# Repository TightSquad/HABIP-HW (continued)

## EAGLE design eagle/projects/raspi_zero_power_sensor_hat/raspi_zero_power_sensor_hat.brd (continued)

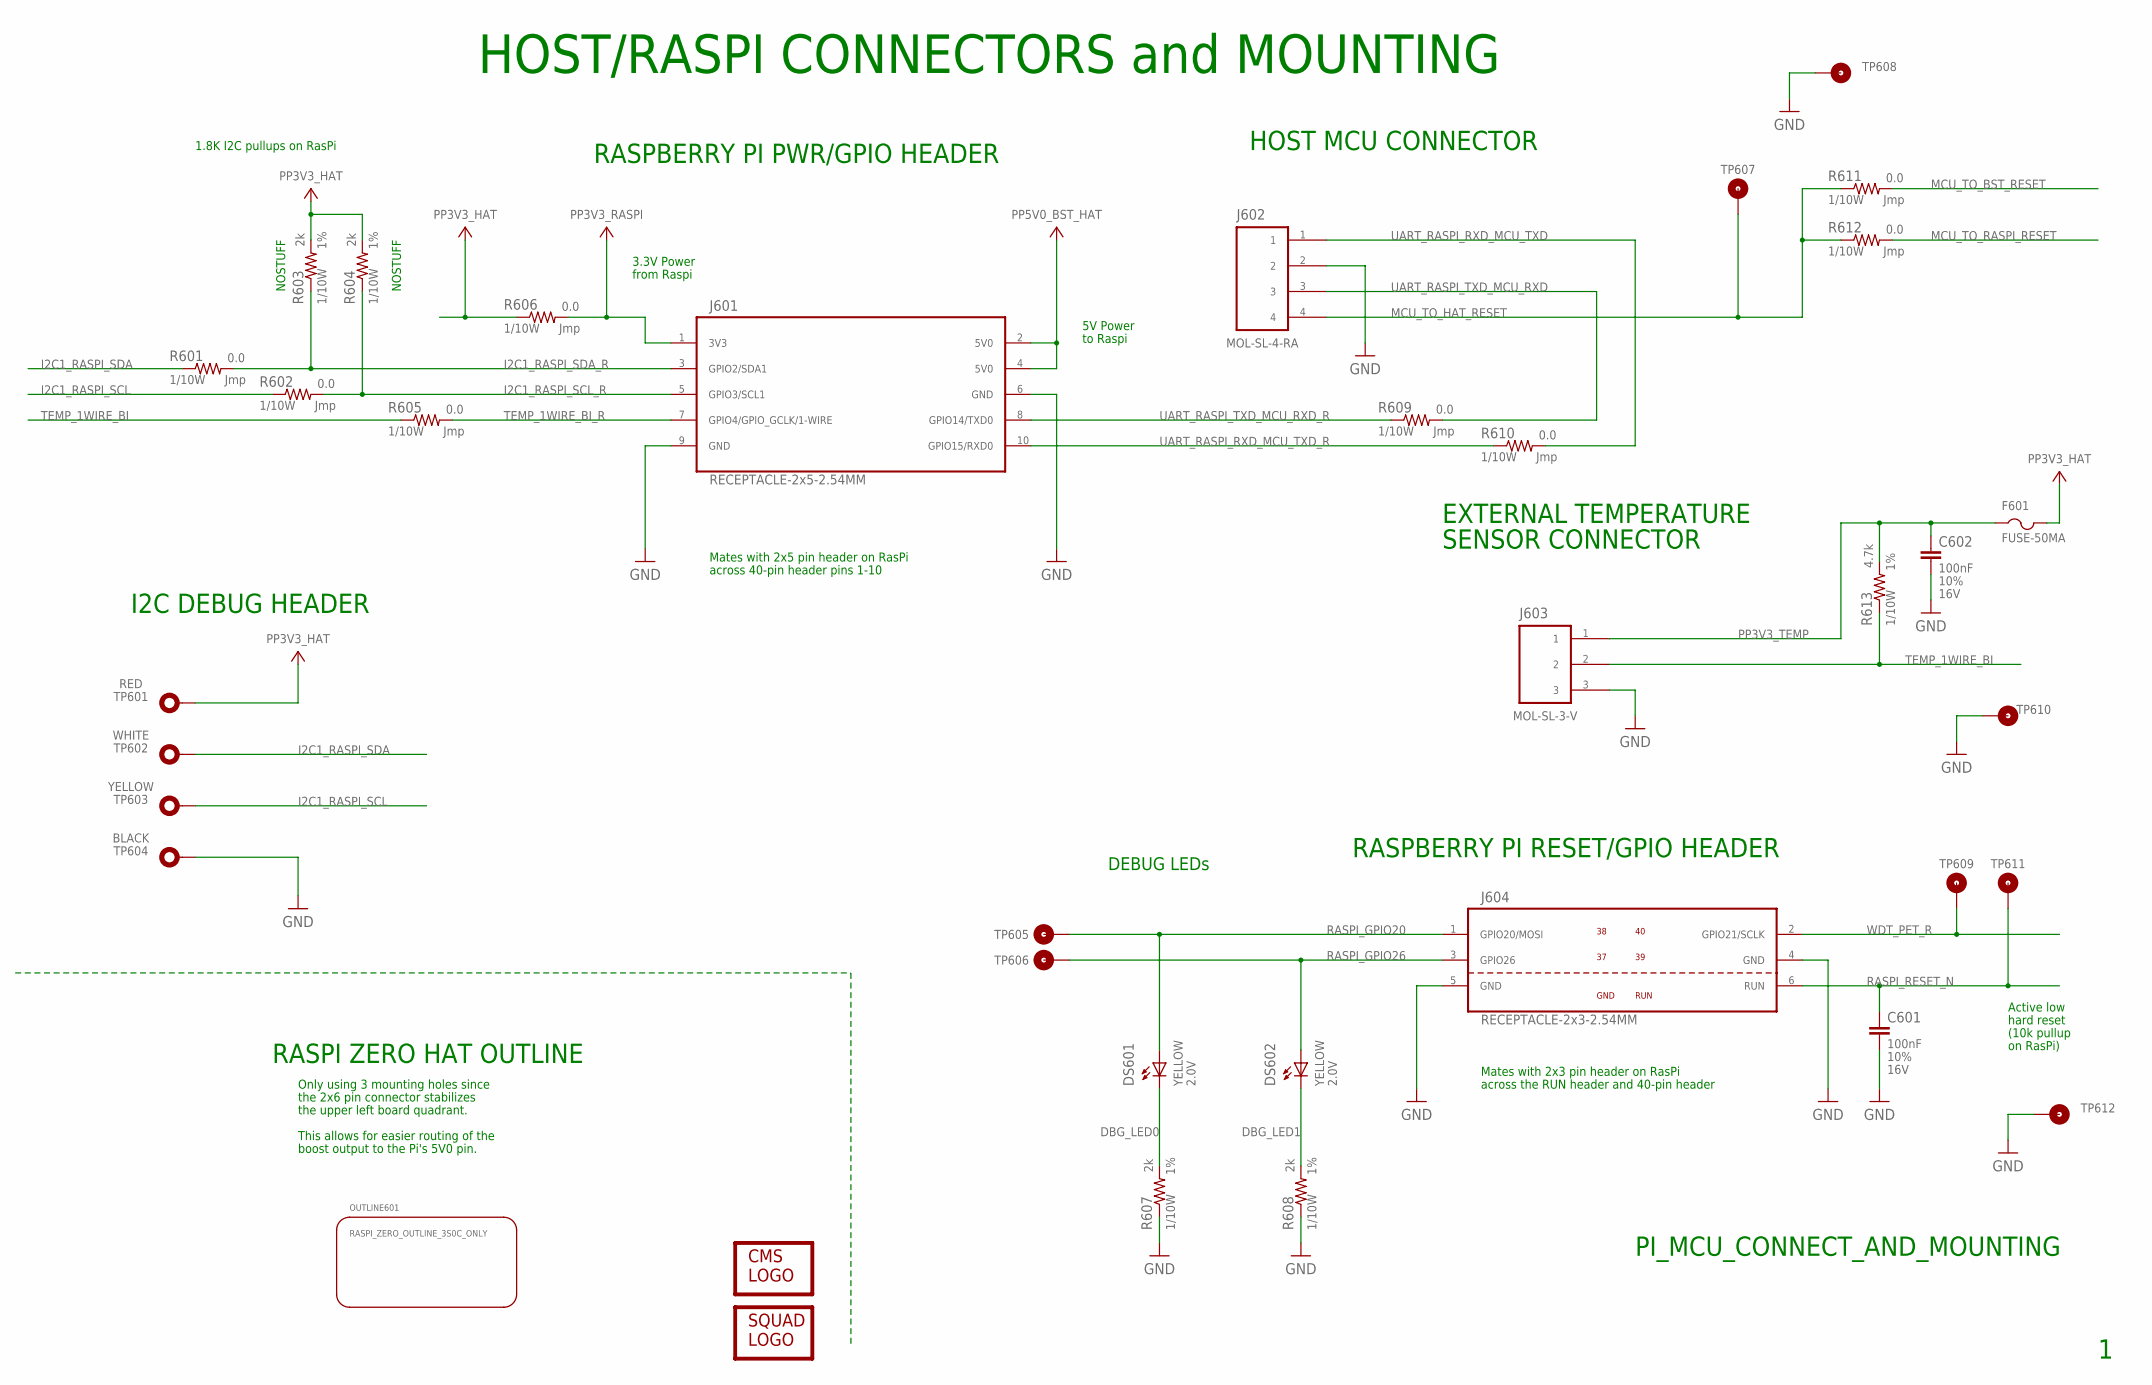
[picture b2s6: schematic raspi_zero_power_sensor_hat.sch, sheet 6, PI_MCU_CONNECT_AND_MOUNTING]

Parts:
C601, C602: 100nF; C0603
DS601, DS602: YELLOW; LED0603
F601: FUSE-50MA; R0603
J601: RECEPTACLE-2x5-2.54MM; RECEPTACLE-2X5-254MM
J602: MOL-SL-4-RA; MOLSL-4-RA_HALF
J603: MOL-SL-3-V; MOLSL-3-V
J604: RECEPTACLE-2x3-2.54MM; RECEPTACLE-2X3-254MM
LOGO601: CMS_LOGO
LOGO602: SQUAD_LOGO
OUTLINE601: RASPI_ZERO_OUTLINE_3S0C_ONLY; RASPI_ZERO_3STANDOFFS_ONLY
R601, R602, R605, R606, R609, R610, R611, R612: 0.0; R0603
R603, R604, R607, R608: 2k; R0603
R613: 4.7k; R0603
TP601: TEST_POINT_TH_D102_R; TP_TH102
TP602: TEST_POINT_TH_D102_W; TP_TH102
TP603: TEST_POINT_TH_D102_Y; TP_TH102
TP604: TEST_POINT_TH_D102_B; TP_TH102
TP605, TP606, TP607, TP608, TP609, TP610, TP611, TP612: TEST_POINT_SMT_15R_SMD; TP15R

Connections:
DBG_LED0: DS601.1 (C), R607.2
DBG_LED1: DS602.1 (C), R608.2
GND: C601.2, C602.2, J601.6 (GND), J601.9 (GND), J602.2, J603.3, J604.4 (GND), J604.5 (GND), R607.1, R608.1, TP604.1, TP608.TP, TP610.TP, TP612.TP; also elsewhere on the board
I2C1_RASPI_SCL: R602.1, TP603.1; also elsewhere on the board
I2C1_RASPI_SCL_R: J601.5 (GPIO3/SCL1), R602.2, R604.1
I2C1_RASPI_SDA: R601.1, TP602.1; also elsewhere on the board
I2C1_RASPI_SDA_R: J601.3 (GPIO2/SDA1), R601.2, R603.1
MCU_TO_BST_RESET: R611.2; also elsewhere on the board
MCU_TO_HAT_RESET: J602.4, R611.1, R612.1, TP607.TP
MCU_TO_RASPI_RESET: R612.2; also elsewhere on the board
PP3V3_HAT: F601.2, R603.2, R604.2, R606.1, TP601.1; also elsewhere on the board
PP3V3_RASPI: J601.1 (3V3), R606.2
PP3V3_TEMP: C602.1, F601.1, J603.1, R613.2
PP5V0_BST_HAT: J601.2 (5V0), J601.4 (5V0); also elsewhere on the board
RASPI_GPIO20: DS601.2 (A), J604.1 (GPIO20/MOSI), TP605.TP
RASPI_GPIO26: DS602.2 (A), J604.3 (GPIO26), TP606.TP
RASPI_RESET_N: C601.1, J604.6 (RUN), TP611.TP; also elsewhere on the board
TEMP_1WIRE_BI: J603.2, R605.1, R613.1
TEMP_1WIRE_BI_R: J601.7 (GPIO4/GPIO_GCLK/1-WIRE), R605.2
UART_RASPI_RXD_MCU_TXD: J602.1, R610.2
UART_RASPI_RXD_MCU_TXD_R: J601.10 (GPIO15/RXD0), R610.1
UART_RASPI_TXD_MCU_RXD: J602.3, R609.2
UART_RASPI_TXD_MCU_RXD_R: J601.8 (GPIO14/TXD0), R609.1
WDT_PET_R: J604.2 (GPIO21/SCLK), TP609.TP; also elsewhere on the board

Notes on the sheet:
PI_MCU_CONNECT_AND_MOUNTING
HOST/RASPI CONNECTORS and MOUNTING
RASPBERRY PI PWR/GPIO HEADER
5V Power
3.3V Power
from Raspi
to Raspi
HOST MCU CONNECTOR
EXTERNAL TEMPERATURE
SENSOR CONNECTOR
RASPI ZERO HAT OUTLINE
Only using 3 mounting holes since
the 2x6 pin connector stabilizes
the upper left board quadrant.
This allows for easier routing of the
boost output to the Pi's 5V0 pin.
I2C DEBUG HEADER
RASPBERRY PI RESET/GPIO HEADER
Active low
hard reset
Mates with 2x3 pin header on RasPi
across the RUN header and 40-pin header
Mates with 2x5 pin header on RasPi
across 40-pin header pins 1-10
NOSTUFF
DEBUG LEDs
(10k pullup
on RasPi)
1.8K I2C pullups on RasPi

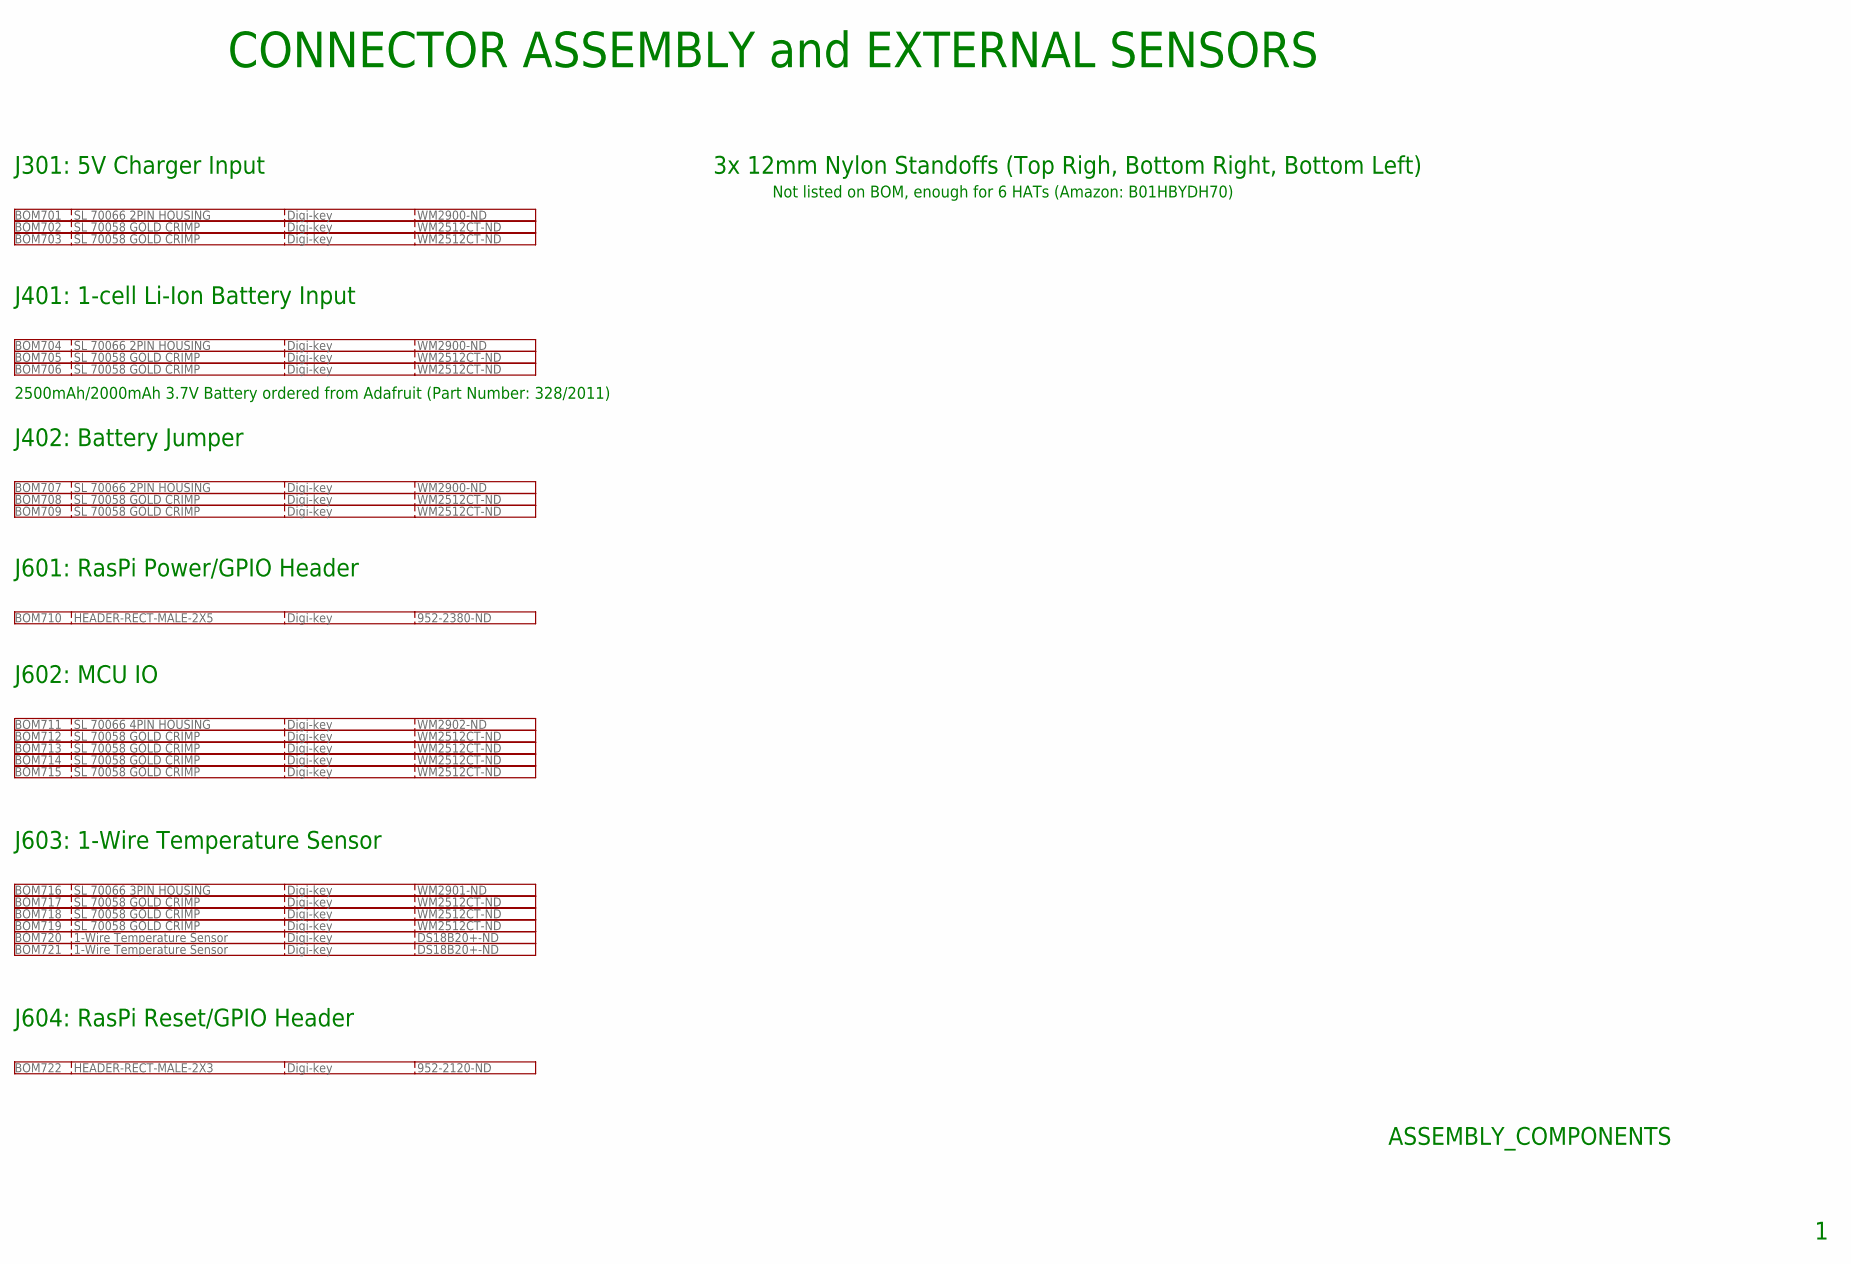
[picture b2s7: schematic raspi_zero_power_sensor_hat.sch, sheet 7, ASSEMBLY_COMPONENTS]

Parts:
BOM701, BOM704, BOM707: SL 70066 2PIN HOUSING; BLANK
BOM702, BOM703, BOM705, BOM706, BOM708, BOM709, BOM712, BOM713, BOM714, BOM715, BOM717, BOM718, BOM719: SL 70058 GOLD CRIMP; BLANK
BOM710: HEADER-RECT-MALE-2X5; BLANK
BOM711: SL 70066 4PIN HOUSING; BLANK
BOM716: SL 70066 3PIN HOUSING; BLANK
BOM720, BOM721: 1-Wire Temperature Sensor; BLANK
BOM722: HEADER-RECT-MALE-2X3; BLANK

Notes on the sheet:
ASSEMBLY_COMPONENTS
CONNECTOR ASSEMBLY and EXTERNAL SENSORS
J301: 5V Charger Input
J401: 1-cell Li-Ion Battery Input
J602: MCU IO
J601: RasPi Power/GPIO Header
J603: 1-Wire Temperature Sensor
J604: RasPi Reset/GPIO Header
3x 12mm Nylon Standoffs (Top Righ, Bottom Right, Bottom Left)
Not listed on BOM, enough for 6 HATs (Amazon: B01HBYDH70)
2500mAh/2000mAh 3.7V Battery ordered from Adafruit (Part Number: 328/2011)
J402: Battery Jumper

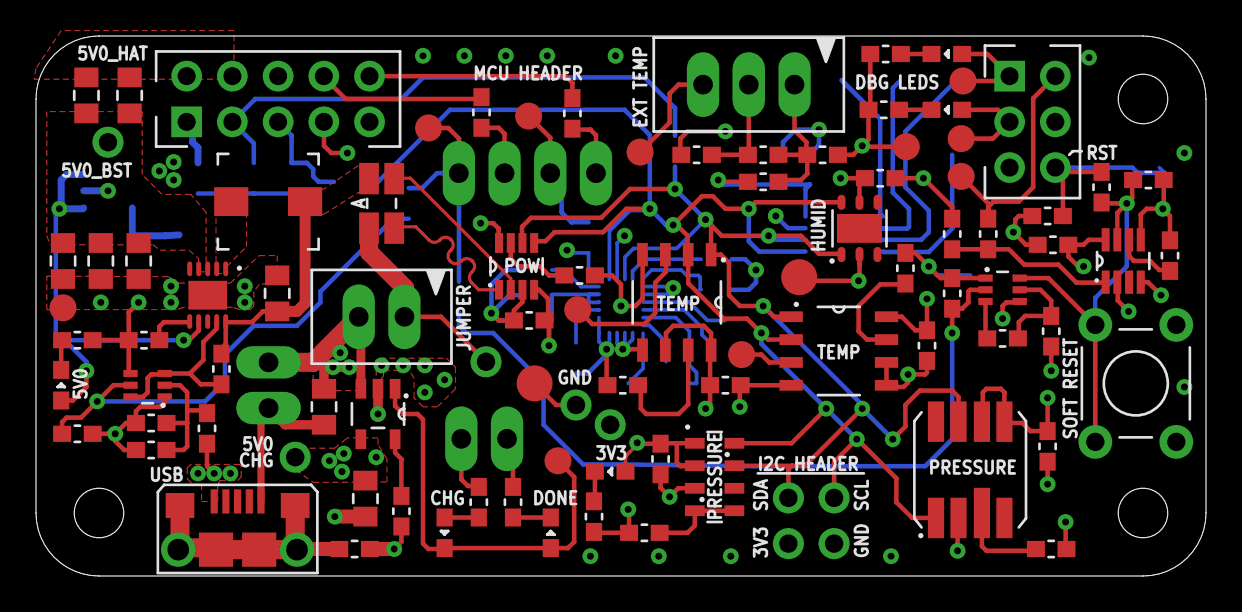
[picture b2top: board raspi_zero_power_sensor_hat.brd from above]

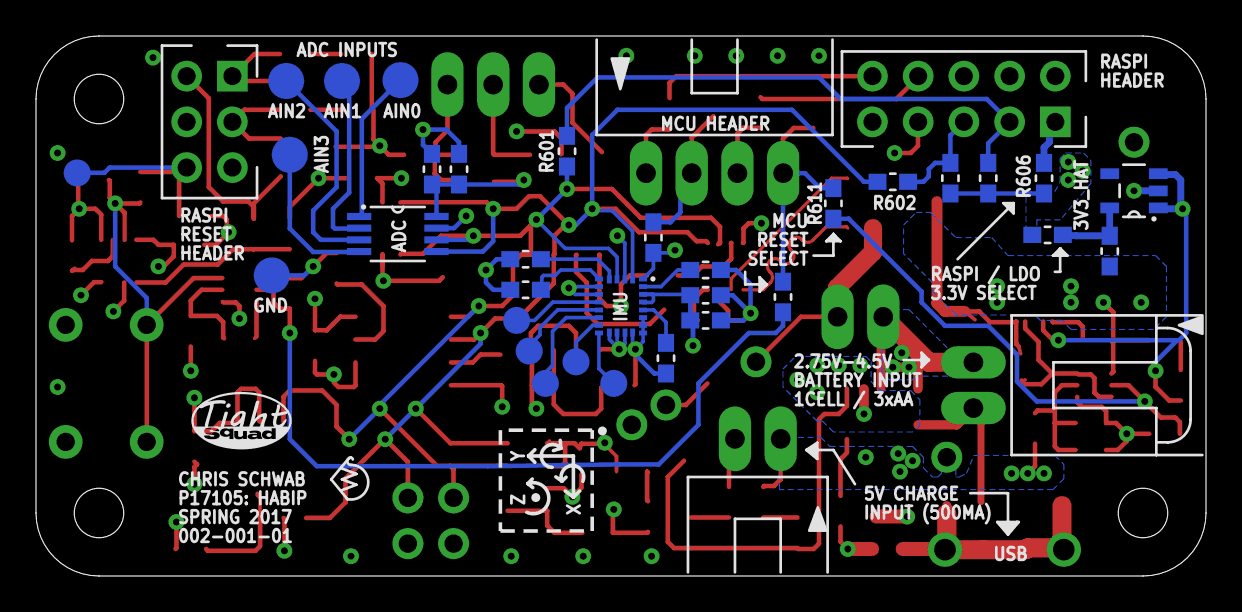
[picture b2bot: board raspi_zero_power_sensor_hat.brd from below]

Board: 4 copper layers, 65.0 x 30.0 mm, 156 parts (37 on the bottom side), 68 nets.

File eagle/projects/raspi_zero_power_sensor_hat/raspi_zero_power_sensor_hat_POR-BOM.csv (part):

"Qty"	"Value"	"Device"	"Package"	"Parts"	"Description"	"ACCURACY"	"ACTUATOR_HEIGHT"	"ACUTATOR_ORIENTATION"	"CIRCUIT"	"CLIPPING"	"COLOR"	"CONTACTS"	"CONTACT_RATING"	"CONTINUOUS_DRAIN_CURRENT"	"CURRENT_DC"	"CURRENT_RATING"	"CURRENT_SAT"	"DATASHEET"	"DCR_MAX"	"DC_COLD_RESISTANCE"	"DIAMETER"	"DRILL"	"FET_TYPE"	"FINISH"	"FORWARD_CURRENT"	"FORWARD_VOLTAGE"	"FUNCTION"	"HEIGHT_BOTTOM"	"HEIGHT_TOP"	"INSULATED"	"INTERFACE"	"LOCKING"	"MANUFACTURER"	"MANUFACTURER_PN"	"MAX_CURRENT"	"MOUNTING_TYPE"	"MOUNT_ANGLE"	"MOUNT_TYPE"	"OUTPUT_ACTIVE"	"OUTPUT_ACTIVE_TIME"	"OUTPUT_BITS"	"OUTPUT_TYPE"	"PITCH"	"PLATING"	"POSITIONS"	"POWER"	"POWER_MAX"	"PRESSURE_TYPE"	"RATED_CURRENT"	"RDS_ON_MAX"	"RESOLUTION"	"RESPONSE_TIME"	"ROWS"	"SHIELDED"	"SRF"	"STARTUP_DELAY"	"SWITCH_FUNCTION"	"TEMP_COEFF"	"TERMINALS"	"TIMEOUT"	"TOLERANCE"	"TP_SIGNAL_NAME"	"VALUE"	"VDS"	"VENDOR"	"VENDOR_PN"	"VGS_MAX"	"VOLTAGE"	"VOLTAGE_RATING"	"_EXTERNAL_"	"VENDOR_PN"	"VGS_MAX"	"VOLTAGE"	"VOLTAGE_RATING"	"_EXTERNAL_"
"3"	"SL 70066 2PIN HOUSING"	"BOM_LINE_ITEM_BLI2"	"BLANK"	"BOM701, BOM704, BOM707"	""	""	""	""	""	""	""	""	""	""	""	""	""	"HW/docs/projects/raspi_zero_power_sensor_hat/datasheets/connectors/uart_1wire_power_battery/050579402_sd.pdf"	""	""	""	""	""	""	""	""	""	""	""	""	""	""	"Molex"	"50-57-9402"	""	""	""	""	""	""	""	""	""	""	""	""	""	""	""	""	""	""	""	""	""	""	""	""	""	""	""	""	"SL 70066 2PIN HOUSING"	""	"Digi-key"	"WM2900-ND"	""	""	""	""	""	""	""	""	""
"13"	"SL 70058 GOLD CRIMP"	"BOM_LINE_ITEM_BLI6"	"BLANK"	"BOM702, BOM703, BOM705, BOM706, BOM708, BOM709, BOM712, BOM713, BOM714, BOM715, BOM717, BOM718, BOM719"	""	""	""	""	""	""	""	""	""	""	""	""	""	"HW/docs/projects/raspi_zero_power_sensor_hat/datasheets/connectors/uart_1wire_power_battery/016020087_sd.pdf"	""	""	""	""	""	""	""	""	""	""	""	""	""	""	"Molex"	"0016020087"	""	""	""	""	""	""	""	""	""	""	""	""	""	""	""	""	""	""	""	""	""	""	""	""	""	""	""	""	"SL 70058 GOLD CRIMP"	""	"Digi-key"	"WM2512CT-ND"	""	""	""	""	""	""	""	""	""
"1"	"HEADER-RECT-MALE-2X5"	"BOM_LINE_ITEM_BLI10"	"BLANK"	"BOM710"	""	""	""	""	""	""	""	""	""	""	""	""	""	"HW/docs/projects/raspi_zero_power_sensor_hat/datasheets/connectors/raspi_header/M20-998.pdf"	""	""	""	""	""	""	""	""	""	""	""	""	""	""	"Harwin"	"M20-9980545"	""	""	""	""	""	""	""	""	""	""	""	""	""	""	""	""	""	""	""	""	""	""	""	""	""	""	""	""	"HEADER-RECT-MALE-2X5"	""	"Digi-key"	"952-2380-ND"	""	""	""	""	""	""	""	""	""
"1"	"SL 70066 4PIN HOUSING"	"BOM_LINE_ITEM_BLI4"	"BLANK"	"BOM711"	""	""	""	""	""	""	""	""	""	""	""	""	""	"HW/docs/projects/raspi_zero_power_sensor_hat/datasheets/connectors/uart_1wire_power_battery/050579402_sd.pdf"	""	""	""	""	""	""	""	""	""	""	""	""	""	""	"Molex"	"0050579404"	""	""	""	""	""	""	""	""	""	""	""	""	""	""	""	""	""	""	""	""	""	""	""	""	""	""	""	""	"SL 70066 4PIN HOUSING"	""	"Digi-key"	"WM2902-ND"	""	""	""	""	""	""	""	""	""
"1"	"SL 70066 3PIN HOUSING"	"BOM_LINE_ITEM_BLI3"	"BLANK"	"BOM716"	""	""	""	""	""	""	""	""	""	""	""	""	""	"HW/docs/projects/raspi_zero_power_sensor_hat/datasheets/connectors/uart_1wire_power_battery/050579402_sd.pdf"	""	""	""	""	""	""	""	""	""	""	""	""	""	""	"Molex"	"50-57-9403"	""	""	""	""	""	""	""	""	""	""	""	""	""	""	""	""	""	""	""	""	""	""	""	""	""	""	""	""	"SL 70066 3PIN HOUSING"	""	"Digi-key"	"WM2901-ND"	""	""	""	""	""	""	""	""	""
"2"	"1-Wire Temperature Sensor"	"BOM_LINE_ITEM_BLI7"	"BLANK"	"BOM720, BOM721"	""	""	""	""	""	""	""	""	""	""	""	""	""	"HW/docs/projects/raspi_zero_power_sensor_hat/datasheets/sensors/DS18B20.pdf"	""	""	""	""	""	""	""	""	""	""	""	""	""	""	"Maxim"	"DS18B20+"	""	""	""	""	""	""	""	""	""	""	""	""	""	""	""	""	""	""	""	""	""	""	""	""	""	""	""	""	"1-Wire Temperature Sensor"	""	"Digi-key"	"DS18B20+-ND"	""	""	""	""	""	""	""	""	""
"1"	"HEADER-RECT-MALE-2X3"	"BOM_LINE_ITEM_BLI1"	"BLANK"	"BOM722"	""	""	""	""	""	""	""	""	""	""	""	""	""	"HW/docs/projects/raspi_zero_power_sensor_hat/datasheets/connectors/raspi_header/M20-998.pdf"	""	""	""	""	""	""	""	""	""	""	""	""	""	""	"Harwin"	"M20-9980345"	""	""	""	""	""	""	""	""	""	""	""	""	""	""	""	""	""	""	""	""	""	""	""	""	""	""	""	""	"HEADER-RECT-MALE-2X3"	""	"Digi-key"	"952-2120-ND"	""	""	""	""	""	""	""	""	""
"5"	"10uF"	"CAP_10UF0_0805_0805"	"C0805"	"C301, C401, C406, C407, C408"	"Chip Capacitor"	""	""	""	""	""	""	""	""	""	""	""	""	"HW/docs/projects/raspi_zero_power_sensor_hat/datasheets/passives/c02e.pdf"	""	""	""	""	""	""	""	""	""	""	""	""	""	""	"Murata"	"GRM21BR61C106KE15L"	""	""	""	""	""	""	""	""	""	""	""	""	""	""	""	""	""	""	""	""	""	""	""	"X5R"	""	""	"10%"	""	"10uF"	""	"Digi-key"	"490-3886-1-ND"	""	"16V"	""	""	""	""	""	""	""
"12"	"100nF"	"CAP_100NF0_0603"	"C0603"	"C302, C501, C502, C506, C507, C508, C510, C511, C512, C513, C601, C602"	"Chip Capacitor"	""	""	""	""	""	""	""	""	""	""	""	""	"HW/docs/projects/raspi_zero_power_sensor_hat/datasheets/passives/c02e.pdf"	""	""	""	""	""	""	""	""	""	""	""	""	""	""	"Murata"	"GRM188R71C104KA01D"	""	""	""	""	""	""	""	""	""	""	""	""	""	""	""	""	""	""	""	""	""	""	""	"X7R"	""	""	"10%"	""	"100nF"	""	"Digi-key"	"490-1532-1-ND"	""	"16V"	""	""	""	""	""	""	""
"1"	"22uF"	"CAP_22UF0_0805"	"C0805"	"C403"	"Chip Capacitor"	""	""	""	""	""	""	""	""	""	""	""	""	"HW/docs/projects/raspi_zero_power_sensor_hat/datasheets/passives/c02e.pdf"	""	""	""	""	""	""	""	""	""	""	""	""	""	""	"Murata"	"GRM21BR61A226ME51L"	""	""	""	""	""	""	""	""	""	""	""	""	""	""	""	""	""	""	""	""	""	""	""	"X5R"	""	""	"20%"	""	"22uF"	""	"Digi-key"	"490-10511-1-ND"	""	"10V"	""	""	""	""	""	""	""
"1"	"18nF"	"CAP_18NF0_0603"	"C0603"	"C405"	"Chip Capacitor"	""	""	""	""	""	""	""	""	""	""	""	""	"HW/docs/projects/raspi_zero_power_sensor_hat/datasheets/passives/c02e.pdf"	""	""	""	""	""	""	""	""	""	""	""	""	""	""	"Murata"	"GRM188R71H183JA01D"	""	""	""	""	""	""	""	""	""	""	""	""	""	""	""	""	""	""	""	""	""	""	""	"X7R"	""	""	"5%"	""	"18nF"	""	"Digi-key"	"490-12544-1-ND"	""	"50V"	""	""	""	""	""	""	""
"1"	"10nF"	"CAP_10NF0_0603"	"C0603"	"C505"	"Chip Capacitor"	""	""	""	""	""	""	""	""	""	""	""	""	"HW/docs/projects/raspi_zero_power_sensor_hat/datasheets/passives/c02e.pdf"	""	""	""	""	""	""	""	""	""	""	""	""	""	""	"Murate"	"GRM188R71H103JA01D"	""	""	""	""	""	""	""	""	""	""	""	""	""	""	""	""	""	""	""	""	""	""	""	"X7R"	""	""	"5%"	""	"10nF"	""	"Digi-key"	"490-9734-1-ND"	""	"50V"	""	""	""	""	""	""	""
"1"	"10uF"	"CAP_10UF0_0603"	"C0603"	"C509"	"Chip Capacitor"	""	""	""	""	""	""	""	""	""	""	""	""	"HW/docs/projects/raspi_zero_power_sensor_hat/datasheets/passives/c02e.pdf"	""	""	""	""	""	""	""	""	""	""	""	""	""	""	"Murata"	"GRM188R61A106KE69D"	""	""	""	""	""	""	""	""	""	""	""	""	""	""	""	""	""	""	""	""	""	""	""	"X5R"	""	""	"10%"	""	"10uF"	""	"Digi-key"	"490-10474-1-ND"	""	"10V"	""	""	""	""	""	""	""
"4"	"YELLOW"	"LED_Y2V0WURTH_0603"	"LED0603"	"DS301, DS402, DS601, DS602"	"Chip LED"	""	""	""	""	""	""	""	""	""	""	""	""	"HW/docs/projects/raspi_zero_power_sensor_hat/datasheets/charger/150060YS75000.pdf"	""	""	""	""	""	""	"20mA"	"2.0V"	""	""	""	""	""	""	"Wurth"	"150060YS75000"	""	""	""	""	""	""	""	""	""	""	""	""	""	""	""	""	""	""	""	""	""	""	""	""	""	""	""	""	"YELLOW"	""	"Digi-key"	"732-4981-1-ND"	""	""	""	""	""	""	""	""	""
"1"	"GREEN"	"LED_G3V2WURTH_0603"	"LED0603"	"DS302"	"Chip LED"	""	""	""	""	""	""	""	""	""	""	""	""	"HW/docs/projects/raspi_zero_power_sensor_hat/datasheets/charger/150060GS75000.pdf"	""	""	""	""	""	""	"20mA"	"3.2V"	""	""	""	""	""	""	"Wurth"	"150060GS75000"	""	""	""	""	""	""	""	""	""	""	""	""	""	""	""	""	""	""	""	""	""	""	""	""	""	""	""	""	"GREEN"	""	"Digi-key"	"732-4971-1-ND"	""	""	""	""	""	""	""	""	""
"1"	"BLUE"	"LED_B3V2WURTH_0603"	"LED0603"	"DS401"	"Chip LED"	""	""	""	""	""	""	""	""	""	""	""	""	"HW/docs/projects/raspi_zero_power_sensor_hat/datasheets/charger/150060BS75000.pdf"	""	""	""	""	""	""	"20mA"	"3.2V"	""	""	""	""	""	""	"Wurth"	"150060BS75000"	""	""	""	""	""	""	""	""	""	""	""	""	""	""	""	""	""	""	""	""	""	""	""	""	""	""	""	""	"BLUE"	""	"Digi-key"	"732-4966-1-ND"	""	""	""	""	""	""	""	""	""
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
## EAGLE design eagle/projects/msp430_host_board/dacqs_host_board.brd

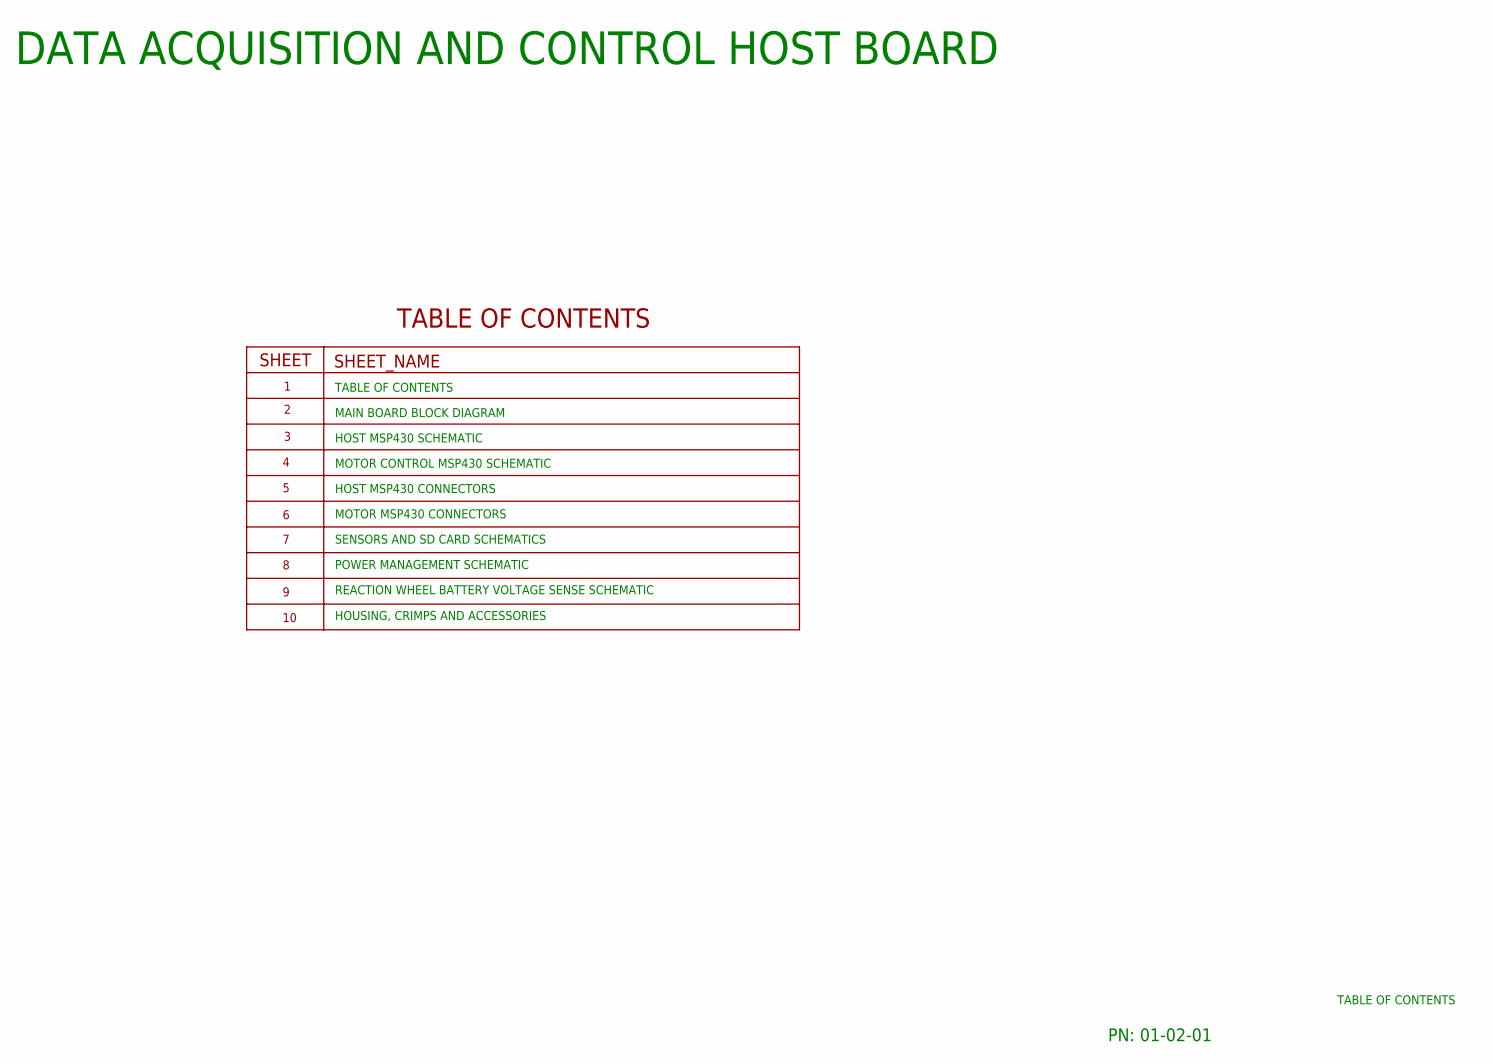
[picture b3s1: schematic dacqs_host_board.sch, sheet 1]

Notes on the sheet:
DATA ACQUISITION AND CONTROL HOST BOARD
TABLE OF CONTENTS
MAIN BOARD BLOCK DIAGRAM
HOST MSP430 SCHEMATIC
MOTOR CONTROL MSP430 SCHEMATIC
HOST MSP430 CONNECTORS
MOTOR MSP430 CONNECTORS
SENSORS AND SD CARD SCHEMATICS
POWER MANAGEMENT SCHEMATIC
REACTION WHEEL BATTERY VOLTAGE SENSE SCHEMATIC
PN: 01-02-01
HOUSING, CRIMPS AND ACCESSORIES

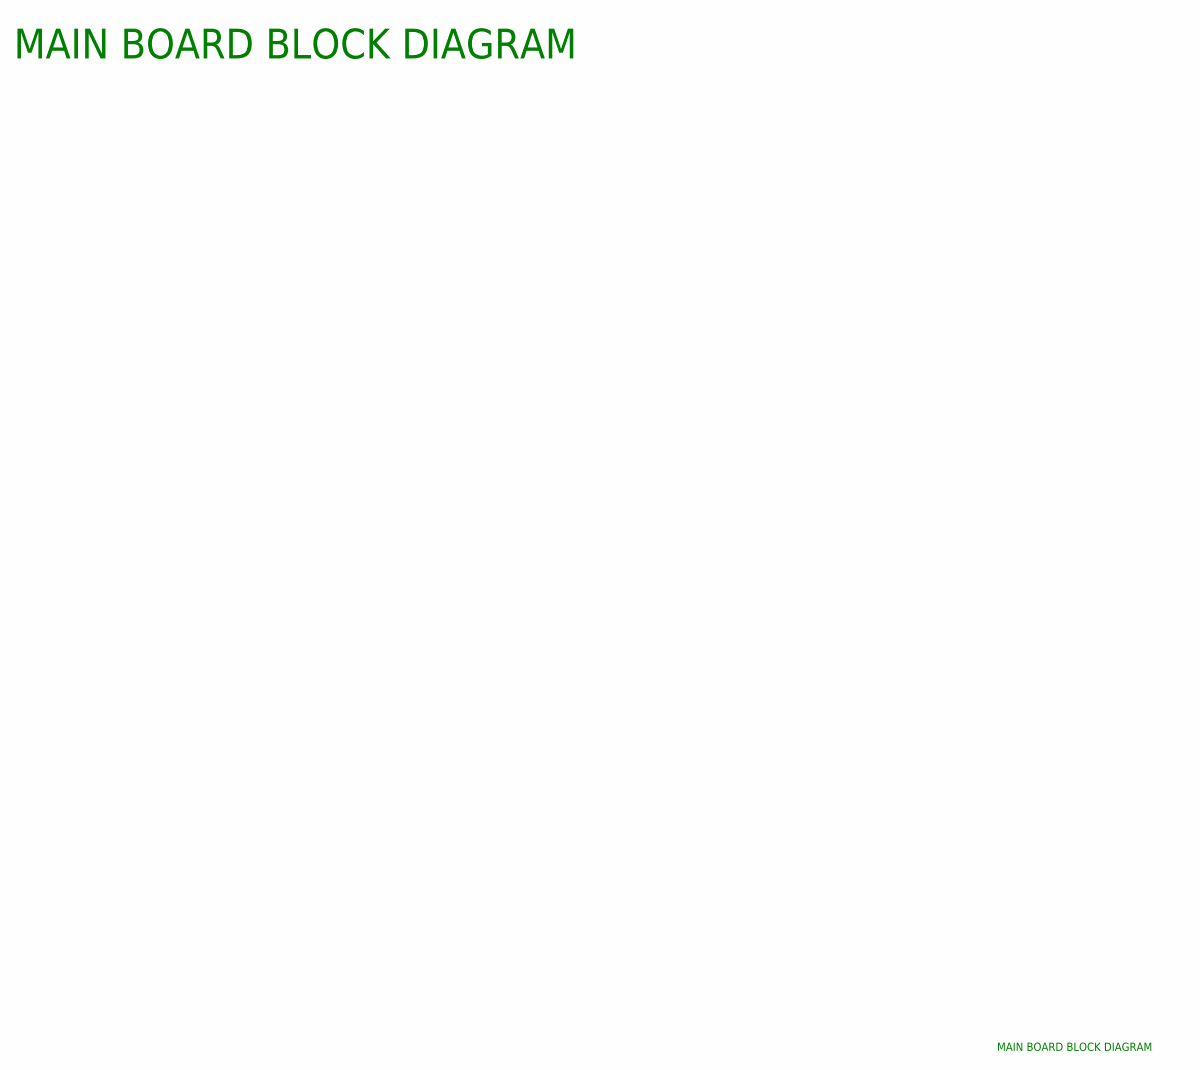
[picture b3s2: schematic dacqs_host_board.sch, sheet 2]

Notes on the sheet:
MAIN BOARD BLOCK DIAGRAM

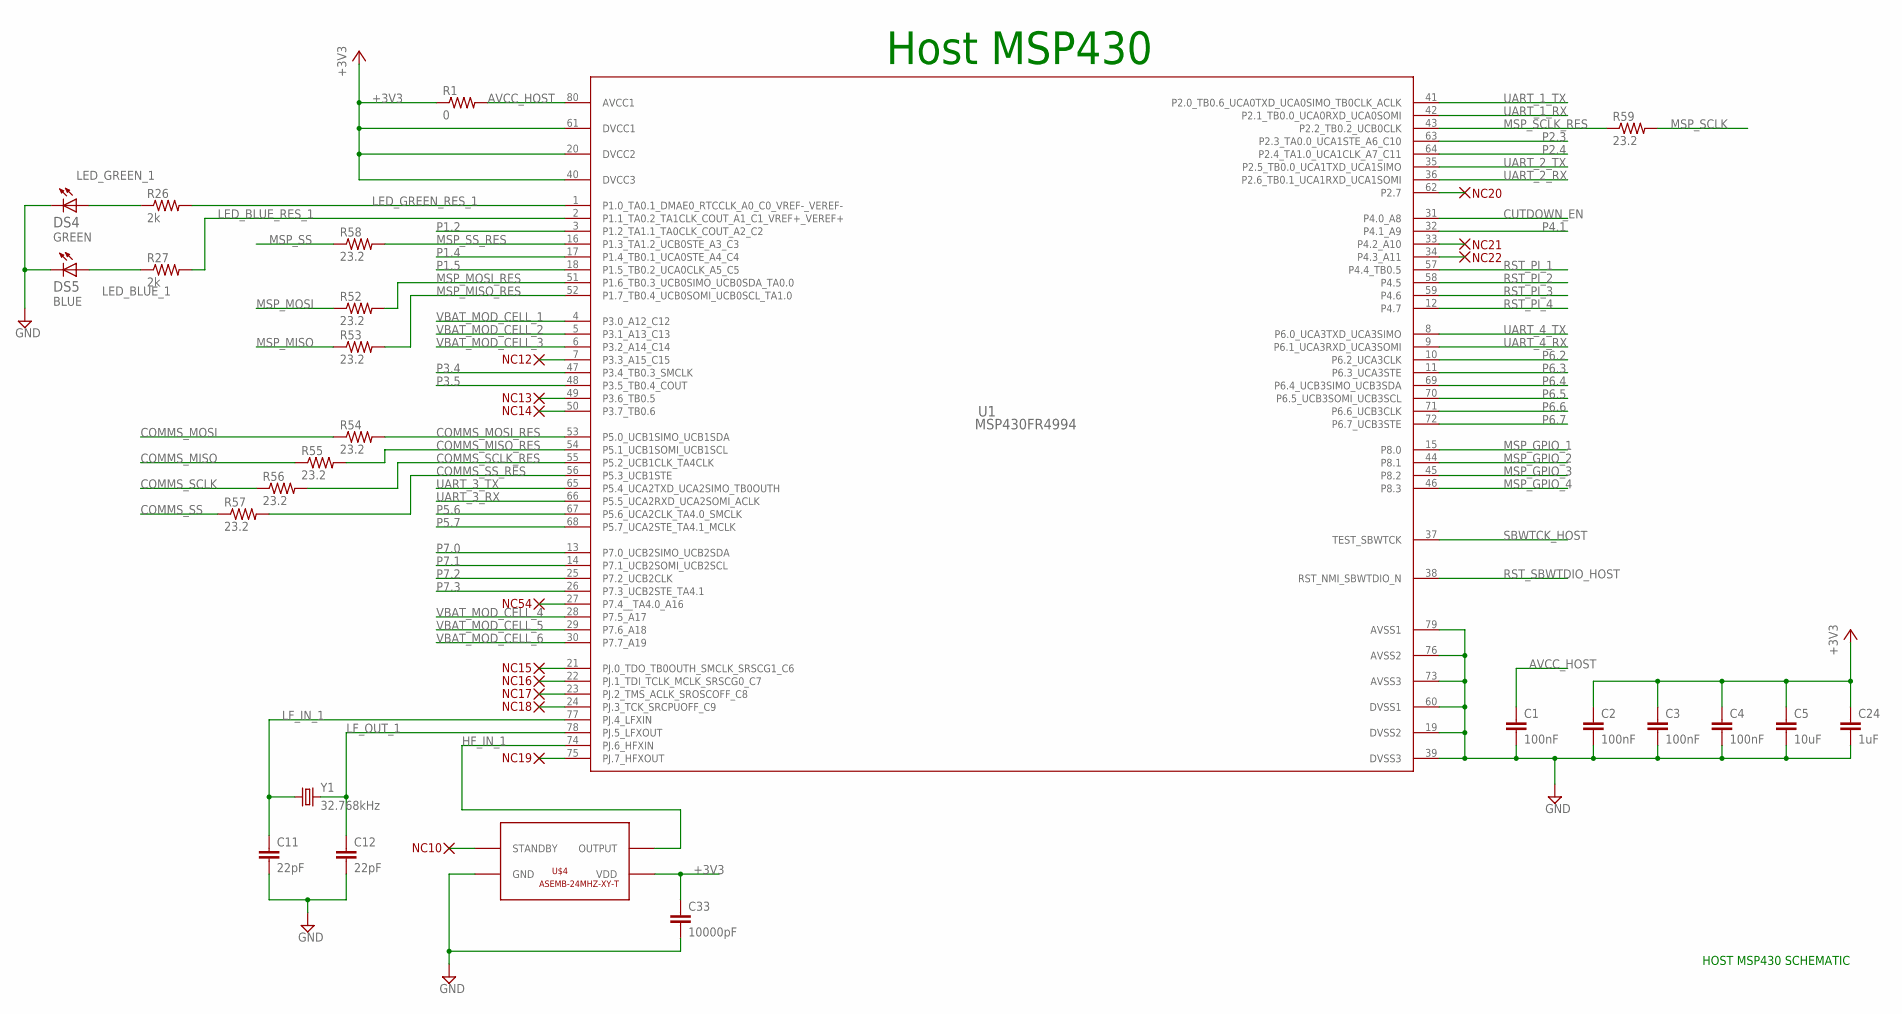
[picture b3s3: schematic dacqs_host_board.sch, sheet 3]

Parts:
C1, C2, C3, C4: 100nF; C0603
C5: 10uF; C0603
C11, C12: 22pF; C0603
C24: 1uF; C0603
C33: 10000pF; C0603
DS4: GREEN; LED0603
DS5: BLUE; LED0603
R1: 0; R0603
R26, R27: 2k; R0603
R52, R53, R54, R55, R56, R57, R58, R59: 23.2; R0603
U1: MSP430FR4994; PN0080A_N
U$4: ASEMB-24MHZ-XY-T; ASEMB-24MHZ-XY-T-PAC
Y1: 32.768kHz; CRYSTAL-SMD-3.2X1.5MM

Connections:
+3V3: C2.1, C3.1, C4.1, C5.1, C24.1, C33.1, R1.1, U1.20 (DVCC2), U1.40 (DVCC3), U1.61 (DVCC1), U$4.P$4 (VDD); also elsewhere on the board
AVCC_HOST: C1.1, R1.2, U1.80 (AVCC1)
COMMS_MISO: R55.1; also elsewhere on the board
COMMS_MISO_RES: R55.2, U1.54 (P5.1_UCB1SOMI_UCB1SCL)
COMMS_MOSI: R54.1; also elsewhere on the board
COMMS_MOSI_RES: R54.2, U1.53 (P5.0_UCB1SIMO_UCB1SDA)
COMMS_SCLK: R56.1; also elsewhere on the board
COMMS_SCLK_RES: R56.2, U1.55 (P5.2_UCB1CLK_TA4CLK)
COMMS_SS: R57.1; also elsewhere on the board
COMMS_SS_RES: R57.2, U1.56 (P5.3_UCB1STE)
CUTDOWN_EN: U1.31 (P4.0_A8); also elsewhere on the board
GND: C1.2, C2.2, C3.2, C4.2, C5.2, C11.2, C12.2, C24.2, C33.2, DS4.1 (C), DS5.1 (C), U1.19 (DVSS2), U1.39 (DVSS3), U1.60 (DVSS1), U1.73 (AVSS3), U1.76 (AVSS2), U1.79 (AVSS1), U$4.P$2 (GND); also elsewhere on the board
HF_IN_1: U1.74 (PJ.6_HFXIN), U$4.P$3 (OUTPUT)
LED_BLUE_1: DS5.2 (A), R27.1
LED_BLUE_RES_1: R27.2, U1.2 (P1.1_TA0.2_TA1CLK_COUT_A1_C1_VREF+_VERE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)
LED_GREEN_1: DS4.2 (A), R26.1
LED_GREEN_RES_1: R26.2, U1.1 (P1.0_TA0.1_DMAE0_RTCCLK_A0_C0_VREF-_VER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)
LF_IN_1: C11.1, U1.77 (PJ.4_LFXIN), Y1.P$1 (1)
LF_OUT_1: C12.1, U1.78 (PJ.5_LFXOUT), Y1.P$2 (2)
MSP_GPIO_1: U1.15 (P8.0); also elsewhere on the board
MSP_GPIO_2: U1.44 (P8.1); also elsewhere on the board
MSP_GPIO_3: U1.45 (P8.2); also elsewhere on the board
MSP_GPIO_4: U1.46 (P8.3); also elsewhere on the board
MSP_MISO: R53.1; also elsewhere on the board
MSP_MISO_RES: R53.2, U1.52 (P1.7_TB0.4_UCB0SOMI_UCB0SCL_TA1.0)
MSP_MOSI: R52.1; also elsewhere on the board
MSP_MOSI_RES: R52.2, U1.51 (P1.6_TB0.3_UCB0SIMO_UCB0SDA_TA0.0)
MSP_SCLK: R59.2; also elsewhere on the board
MSP_SCLK_RES: R59.1, U1.43 (P2.2_TB0.2_UCB0CLK)
MSP_SS: R58.1; also elsewhere on the board
MSP_SS_RES: R58.2, U1.16 (P1.3_TA1.2_UCB0STE_A3_C3)
P1.2: U1.3 (P1.2_TA1.1_TA0CLK_COUT_A2_C2); also elsewhere on the board
P1.4: U1.17 (P1.4_TB0.1_UCA0STE_A4_C4); also elsewhere on the board
P1.5: U1.18 (P1.5_TB0.2_UCA0CLK_A5_C5); also elsewhere on the board
P2.3: U1.63 (P2.3_TA0.0_UCA1STE_A6_C10)
P2.4: U1.64 (P2.4_TA1.0_UCA1CLK_A7_C11)
P3.4: U1.47 (P3.4_TB0.3_SMCLK)
P3.5: U1.48 (P3.5_TB0.4_COUT)
P4.1: U1.32 (P4.1_A9)
P5.6: U1.67 (P5.6_UCA2CLK_TA4.0_SMCLK)
P5.7: U1.68 (P5.7_UCA2STE_TA4.1_MCLK)
P6.2: U1.10 (P6.2_UCA3CLK); also elsewhere on the board
P6.3: U1.11 (P6.3_UCA3STE); also elsewhere on the board
P6.4: U1.69 (P6.4_UCB3SIMO_UCB3SDA); also elsewhere on the board
P6.5: U1.70 (P6.5_UCB3SOMI_UCB3SCL); also elsewhere on the board
P6.6: U1.71 (P6.6_UCB3CLK); also elsewhere on the board
P6.7: U1.72 (P6.7_UCB3STE); also elsewhere on the board
P7.0: U1.13 (P7.0_UCB2SIMO_UCB2SDA); also elsewhere on the board
P7.1: U1.14 (P7.1_UCB2SOMI_UCB2SCL); also elsewhere on the board
P7.2: U1.25 (P7.2_UCB2CLK); also elsewhere on the board
P7.3: U1.26 (P7.3_UCB2STE_TA4.1); also elsewhere on the board
RST_PI_1: U1.57 (P4.4_TB0.5); also elsewhere on the board
RST_PI_2: U1.58 (P4.5); also elsewhere on the board
RST_PI_3: U1.59 (P4.6); also elsewhere on the board
RST_PI_4: U1.12 (P4.7); also elsewhere on the board
RST_SBWTDIO_HOST: U1.38 (RST_NMI_SBWTDIO_N); also elsewhere on the board
SBWTCK_HOST: U1.37 (TEST_SBWTCK); also elsewhere on the board
UART_1_RX: U1.42 (P2.1_TB0.0_UCA0RXD_UCA0SOMI); also elsewhere on the board
UART_1_TX: U1.41 (P2.0_TB0.6_UCA0TXD_UCA0SIMO_TB0CLK_ACLK); also elsewhere on the board
UART_2_RX: U1.36 (P2.6_TB0.1_UCA1RXD_UCA1SOMI); also elsewhere on the board
UART_2_TX: U1.35 (P2.5_TB0.0_UCA1TXD_UCA1SIMO); also elsewhere on the board
UART_3_RX: U1.66 (P5.5_UCA2RXD_UCA2SOMI_ACLK); also elsewhere on the board
UART_3_TX: U1.65 (P5.4_UCA2TXD_UCA2SIMO_TB0OUTH); also elsewhere on the board
UART_4_RX: U1.9 (P6.1_UCA3RXD_UCA3SOMI); also elsewhere on the board
UART_4_TX: U1.8 (P6.0_UCA3TXD_UCA3SIMO); also elsewhere on the board
VBAT_MOD_CELL_1: U1.4 (P3.0_A12_C12); also elsewhere on the board
VBAT_MOD_CELL_2: U1.5 (P3.1_A13_C13); also elsewhere on the board
VBAT_MOD_CELL_3: U1.6 (P3.2_A14_C14); also elsewhere on the board
VBAT_MOD_CELL_4: U1.28 (P7.5_A17); also elsewhere on the board
VBAT_MOD_CELL_5: U1.29 (P7.6_A18); also elsewhere on the board
VBAT_MOD_CELL_6: U1.30 (P7.7_A19); also elsewhere on the board

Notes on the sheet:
Host MSP430
HOST MSP430 SCHEMATIC
